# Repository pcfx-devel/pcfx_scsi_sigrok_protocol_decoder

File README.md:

# pcfx_scsi_sigrok_protocol_decoder
Protocol decoder for sigrok/pulseview-based logic state analyzers for decoding SCSI data

## Introduction

The PC-FX uses SCSI to communicate to the internal CDROM (and potentially other devices).
This data can be seen travelling between the PC-FX main board and the CDROM daughterboard,
along with a few additional signals.

## The Protocol Decoder

### How To Install

On DSView, there is a folder called 'decoders' within the application folder for DSView; within this
folder are subfolders for each protocol decoder. Copy the 'pcfx-scsi' folder here into its corresponding
location in the application subfolder.  (For PulseView or other sigrok-compatible software, consult the
application's instructions).

### How To Use

Once you have installed the protocol decoder, it should be selectable in the list of protocol decoders.

The protocol decoder adds several annotation rows, to be able to interpret the bitstream in several
different ways; each of them can be displayed or suppressed.  These rows include:
 - SCSI phase (which defines which unit(s) are communicating what type of data to each other)
 - Type (either LUN pairs for communication, or a communication type within "Information Transfer" bus phase)
 - Data To Target (data bytes being sent from the Master to the Target)
 - Data From Target (data bytes being sent from the Target to the Master)
 - Byte Number (Counter for bytes within a transfer sequence)

An example is shown below (from an actual data capture):

### Not Implemented

- SCSI Abort
- It is currently not paying attention to the SCSI "ATN" signal
- Any Timing/timeout conditions (bus settling, timeouts, etc.)
- Any other Protocol Errors

### What exactly is this 'sigrok' thing ?

The sigrok project aims at creating a portable, cross-platform, Free/Libre/Open-Source signal analysis software suite that supports
various device types (e.g. logic analyzers, oscilloscopes, and many more).
(taken from [the project's home page](https://sigrok.org/wiki/Main_Page) )

The specification for protocol analyzers (for logic state analysis) is extensible and there are many
example protocols available.

### Why write a decoder ?

I had already done signal captures and understood the meanings of some state transitions of the signals for PC-FX SCSI,
but I needed to understand more about the SCSI standard, and how it was implemented on the PC-FX.

However, it was quite tedious trying to interpret the bit values and see "the bigger picture", and I wished I had a
protocol decoder like this one to help interpret.

## NOTES:

While this protocol decoder has been written according to sigrok standards, I have (so far) only
installed and tested on "DSView", used in conjunction with my DreamSource Labs' DSLogic U3Pro32
logic state analyzer, and not PulseView.

I have not yet submitted this into the sigrok project, as there are still some framing error
conditions I'd like to identify and display, and I want to do testing on the actual PulseView
software first.

I also may wish to do a little more code cleanup before submission.  I'm not familiar with their
review process, so I have no idea how long it will take to be approved (or receive feedback).

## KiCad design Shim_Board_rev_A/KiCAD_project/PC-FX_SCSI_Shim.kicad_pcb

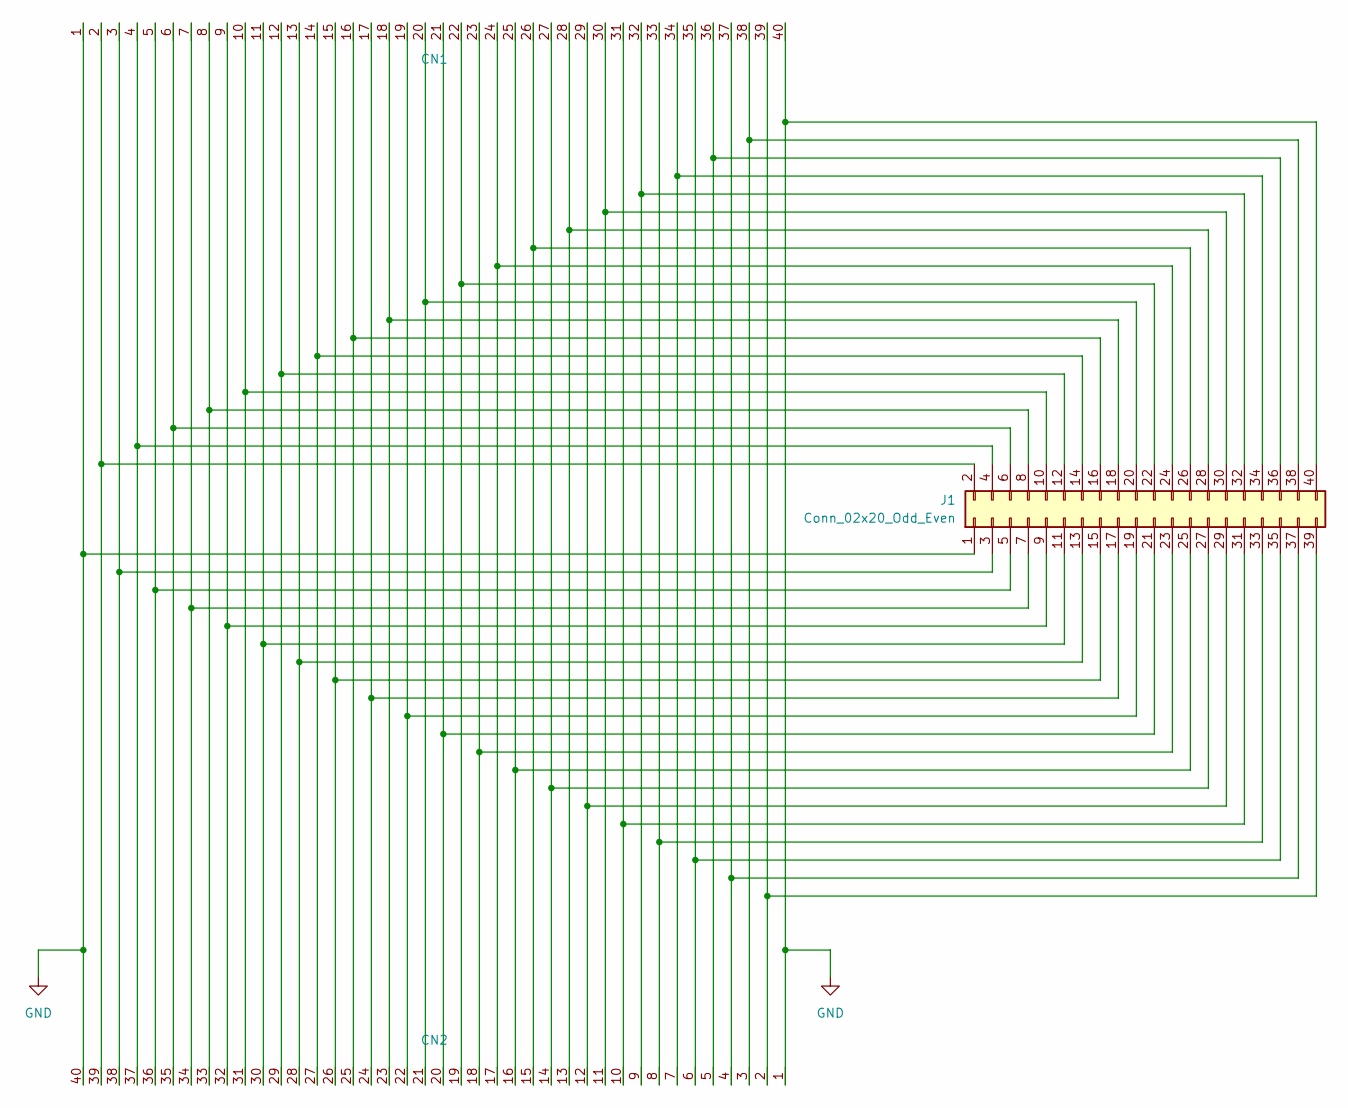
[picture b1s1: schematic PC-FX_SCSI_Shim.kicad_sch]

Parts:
CN1, CN2: FFC_40_Molex_52044-4045
J1: Conn_02x20_Odd_Even; PinHeader_2x20_P2.54mm_Vertical

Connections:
GND: CN1.1, CN1.40, CN2.1, CN2.40, J1.1, J1.40
unnamed: CN1.2, CN2.39, J1.2
unnamed: CN1.3, CN2.38, J1.3
unnamed: CN1.4, CN2.37, J1.4
unnamed: CN1.5, CN2.36, J1.5
unnamed: CN1.6, CN2.35, J1.6
unnamed: CN1.7, CN2.34, J1.7
unnamed: CN1.8, CN2.33, J1.8
unnamed: CN1.9, CN2.32, J1.9
unnamed: CN1.10, CN2.31, J1.10
unnamed: CN1.11, CN2.30, J1.11
unnamed: CN1.12, CN2.29, J1.12
unnamed: CN1.13, CN2.28, J1.13
unnamed: CN1.14, CN2.27, J1.14
unnamed: CN1.15, CN2.26, J1.15
unnamed: CN1.16, CN2.25, J1.16
unnamed: CN1.17, CN2.24, J1.17
unnamed: CN1.18, CN2.23, J1.18
unnamed: CN1.19, CN2.22, J1.19
unnamed: CN1.20, CN2.21, J1.20
unnamed: CN1.21, CN2.20, J1.21
unnamed: CN1.22, CN2.19, J1.22
unnamed: CN1.23, CN2.18, J1.23
unnamed: CN1.24, CN2.17, J1.24
unnamed: CN1.25, CN2.16, J1.25
unnamed: CN1.26, CN2.15, J1.26
unnamed: CN1.27, CN2.14, J1.27
unnamed: CN1.28, CN2.13, J1.28
unnamed: CN1.29, CN2.12, J1.29
unnamed: CN1.30, CN2.11, J1.30
unnamed: CN1.31, CN2.10, J1.31
unnamed: CN1.32, CN2.9, J1.32
unnamed: CN1.33, CN2.8, J1.33
unnamed: CN1.34, CN2.7, J1.34
unnamed: CN1.35, CN2.6, J1.35
unnamed: CN1.36, CN2.5, J1.36
unnamed: CN1.37, CN2.4, J1.37
unnamed: CN1.38, CN2.3, J1.38
unnamed: CN1.39, CN2.2, J1.39

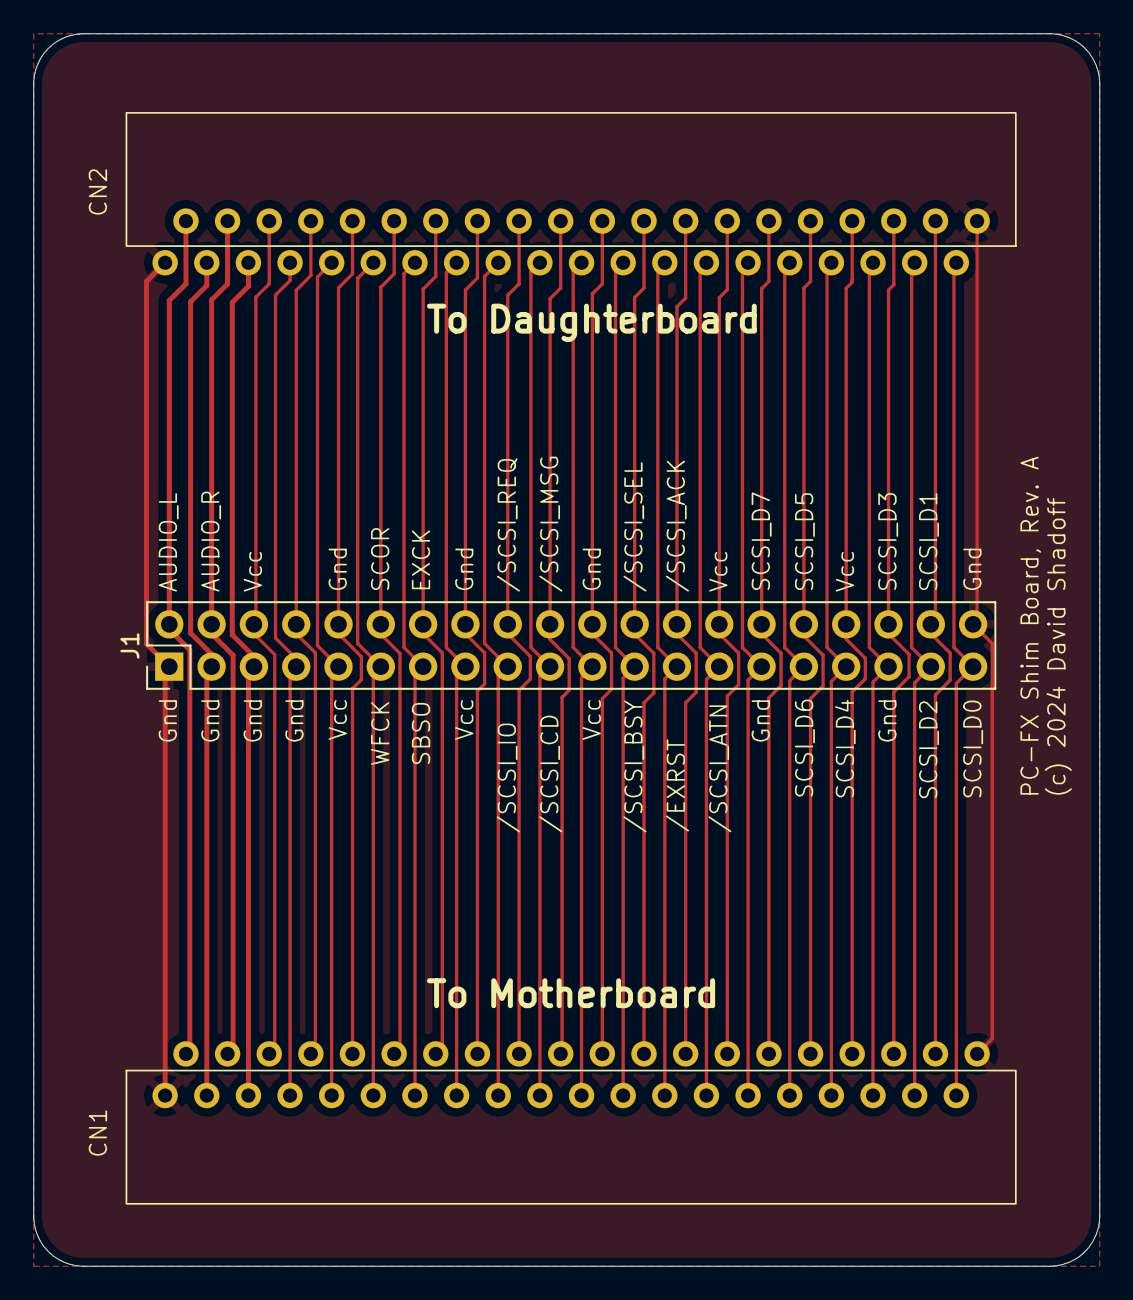
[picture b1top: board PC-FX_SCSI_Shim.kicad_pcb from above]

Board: 2 copper layers, 64.0 x 74.0 mm, 3 parts (0 on the bottom side), 39 nets.

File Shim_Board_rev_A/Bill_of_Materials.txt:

CN1,CN2: Molex 52044-4045 FFC 40-pin connector
J1: 2x2 Pin Header, 2.54mm (0.1") spacing

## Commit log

2024-08-25 Add glitch filter on BSY line
2024-08-27 Add byte counter, remove scsi_req from channels, still need glitch filter
2024-08-27 Add glitch filter (working), but prior to cleanup
2024-08-27 Clean code
2024-08-27 Add some traces
2024-08-27 More captures
2024-08-28 Fix bug in glitch filter, color-code some SCSI commands, add SCSI command list
2024-08-29 Fix bug reading most significant bit, also categorize code 0x4B
2024-09-02 Add PC Board for the capture of traffic
2024-09-03 Add datasheet
2024-12-02 Add additional information about SCSI Commands in COMMAND phase
2024-12-03 More Command annotations
2024-12-27 Gather more samples - boot related
2025-01-01 ABORT Transfer scenario
2025-01-06 Define signals within PCFX_SCSI sigrok decoder
2025-01-30 FFC 3d model added
2025-04-14 Add some learning from PC Engine decoder

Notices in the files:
Shim_Board_rev_A/KiCAD_project/PC-FX_SCSI_Shim.kicad_pcb:
(c) 2024 David Shadoff
